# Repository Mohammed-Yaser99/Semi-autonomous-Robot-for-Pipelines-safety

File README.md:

This repository contains working files of a Semi-Autonomous Pipline Inspection robot "RC-XD" :
- Code files for : Arduino mega , Arduino Uno , Rasperry-pi , V-rep simulation
- PCBS design 
- Presenation and Report for detailed aspects and study cases of the project
- Video for the V-rep simulation

- Pipeline systems deteriorate progressively over time through various means.
- This product aims to create a pipeline inspection robot that has an adaptable structure to the pipe diameter, and cheap at the same time.
- Pipeline inspection robots are designed to act in inaccessible environment and also to remove the human factor from labour intensive or dangerous work environments. 
- Our challenge is to make this robot adaptable to pipe diameters varying from 450mm to 700mm with an adjustable probe mount.

- Adjustable diameter range (45-70 cm)
- Long travel ranges up to 30m
- Crack identification 
- Shape identification for cracks 
- Locating crack places
- Live video record 
- Electrically insulated 
- Scratch free wheels and safe to pipes insulation materials 
- Easy to transport 
- Easy interface

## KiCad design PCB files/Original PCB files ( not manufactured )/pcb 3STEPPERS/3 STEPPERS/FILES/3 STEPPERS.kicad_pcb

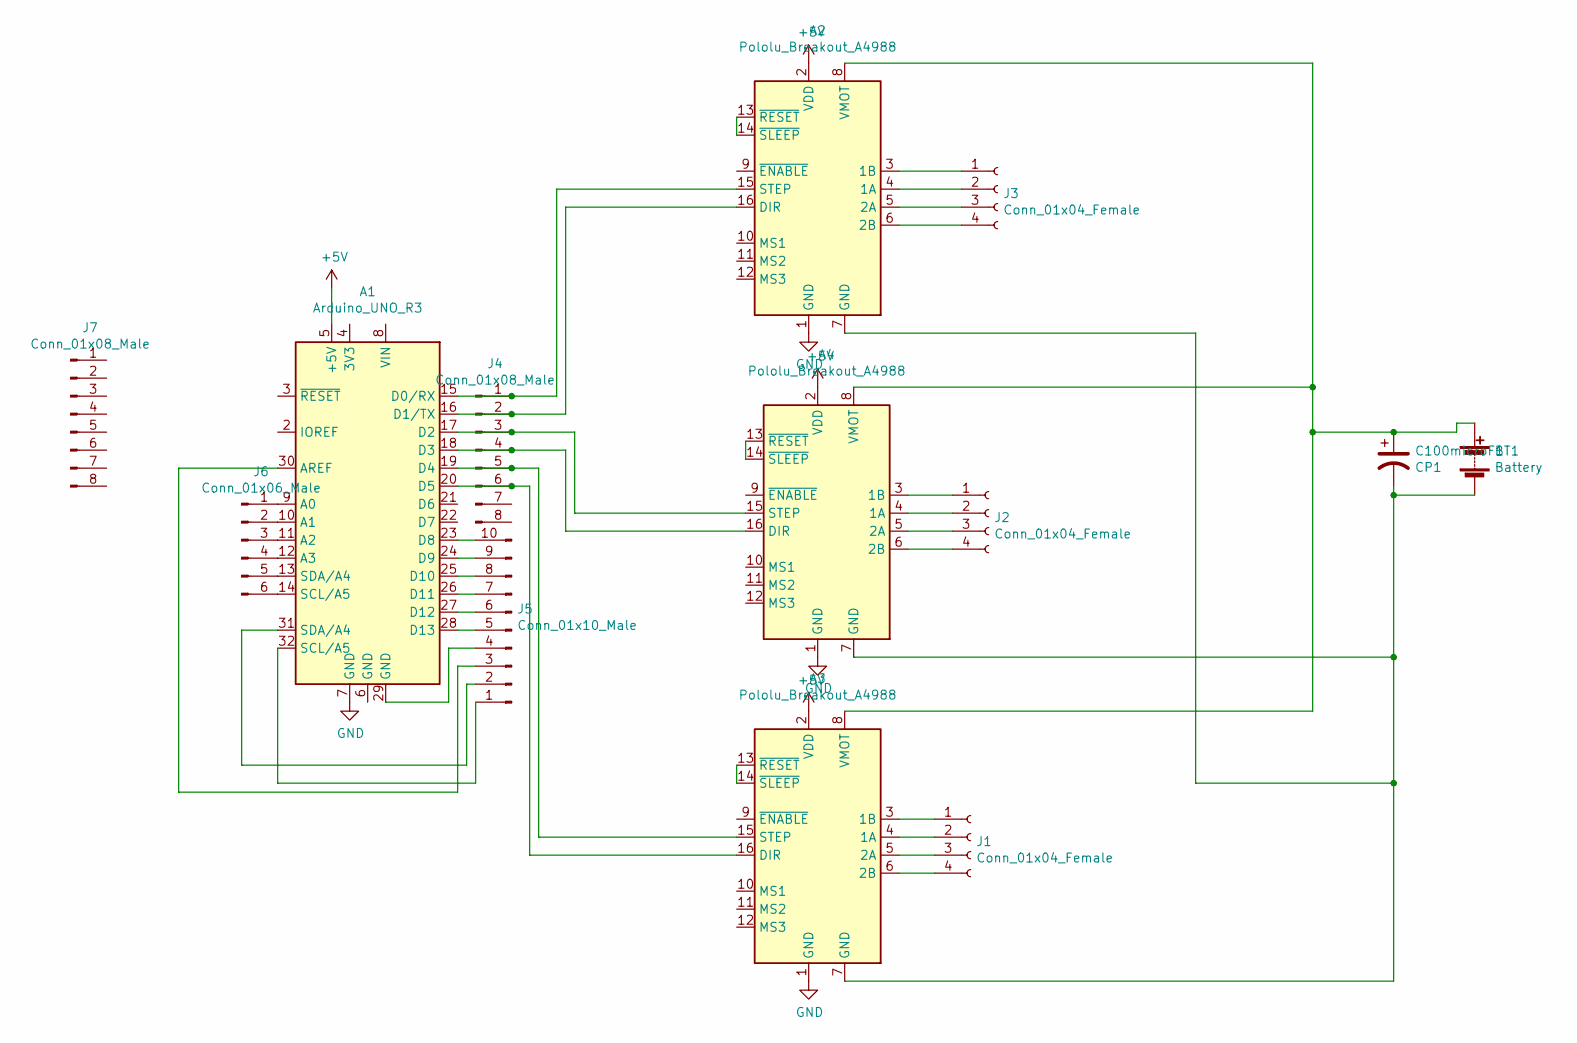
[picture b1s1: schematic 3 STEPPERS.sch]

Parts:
A1: Arduino_UNO_R3
A2, A3, A4: Pololu_Breakout_A4988; Pololu_Breakout-16_15.2x20.3mm
BT1: Battery; TerminalBlock_Phoenix_MKDS-1,5-2_1x02_P5.00mm_Horizontal
C100microF1: CP1; CP_Radial_D12.5mm_P7.50mm
J1, J2, J3: Conn_01x04_Female; PinSocket_1x04_P1.00mm_Vertical
J4, J7: Conn_01x08_Male; PinHeader_1x08_P2.54mm_Vertical
J5: Conn_01x10_Male; PinHeader_1x10_P2.54mm_Vertical
J6: Conn_01x06_Male; PinHeader_1x06_P2.54mm_Vertical

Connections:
+5V: A1.5 (+5V), A2.2 (VDD), A3.2 (VDD), A4.2 (VDD)
GND: A1.7 (GND), A2.1 (GND), A3.1 (GND), A4.1 (GND)
unnamed: A1.9 (A0), J6.1
unnamed: A1.10 (A1), J6.2
unnamed: A1.11 (A2), J6.3
unnamed: A1.12 (A3), J6.4
unnamed: A1.13 (SDA/A4), J6.5
unnamed: A1.14 (SCL/A5), J6.6
unnamed: A1.15 (D0/RX), A2.15 (STEP), J4.1
unnamed: A1.16 (D1/TX), A2.16 (DIR), J4.2
unnamed: A1.17 (D2), A4.15 (STEP), J4.3
unnamed: A1.18 (D3), A4.16 (DIR), J4.4
unnamed: A1.19 (D4), A3.15 (STEP), J4.5
unnamed: A1.20 (D5), A3.16 (DIR), J4.6
unnamed: A1.23 (D8), J5.10
unnamed: A1.24 (D9), J5.9
unnamed: A1.25 (D10), J5.8
unnamed: A1.26 (D11), J5.7
unnamed: A1.27 (D12), J5.6
unnamed: A1.28 (D13), J5.5
unnamed: A1.29 (GND), J5.4
unnamed: A1.30 (AREF), J5.3
unnamed: A1.31 (SDA/A4), J5.2
unnamed: A1.32 (SCL/A5), J5.1
unnamed: A2.3 (1B), J3.1
unnamed: A2.4 (1A), J3.2
unnamed: A2.5 (2A), J3.3
unnamed: A2.6 (2B), J3.4
unnamed: A2.7 (GND), A3.7 (GND), A4.7 (GND), BT1.2 (-), C100microF1.2
unnamed: A2.8 (VMOT), A3.8 (VMOT), A4.8 (VMOT), BT1.1 (+), C100microF1.1
unnamed: A2.13 (~RESET), A2.14 (~SLEEP)
unnamed: A3.3 (1B), J1.1
unnamed: A3.4 (1A), J1.2
unnamed: A3.5 (2A), J1.3
unnamed: A3.6 (2B), J1.4
unnamed: A3.13 (~RESET), A3.14 (~SLEEP)
unnamed: A4.3 (1B), J2.1
unnamed: A4.4 (1A), J2.2
unnamed: A4.5 (2A), J2.3
unnamed: A4.6 (2B), J2.4
unnamed: A4.13 (~RESET), A4.14 (~SLEEP)

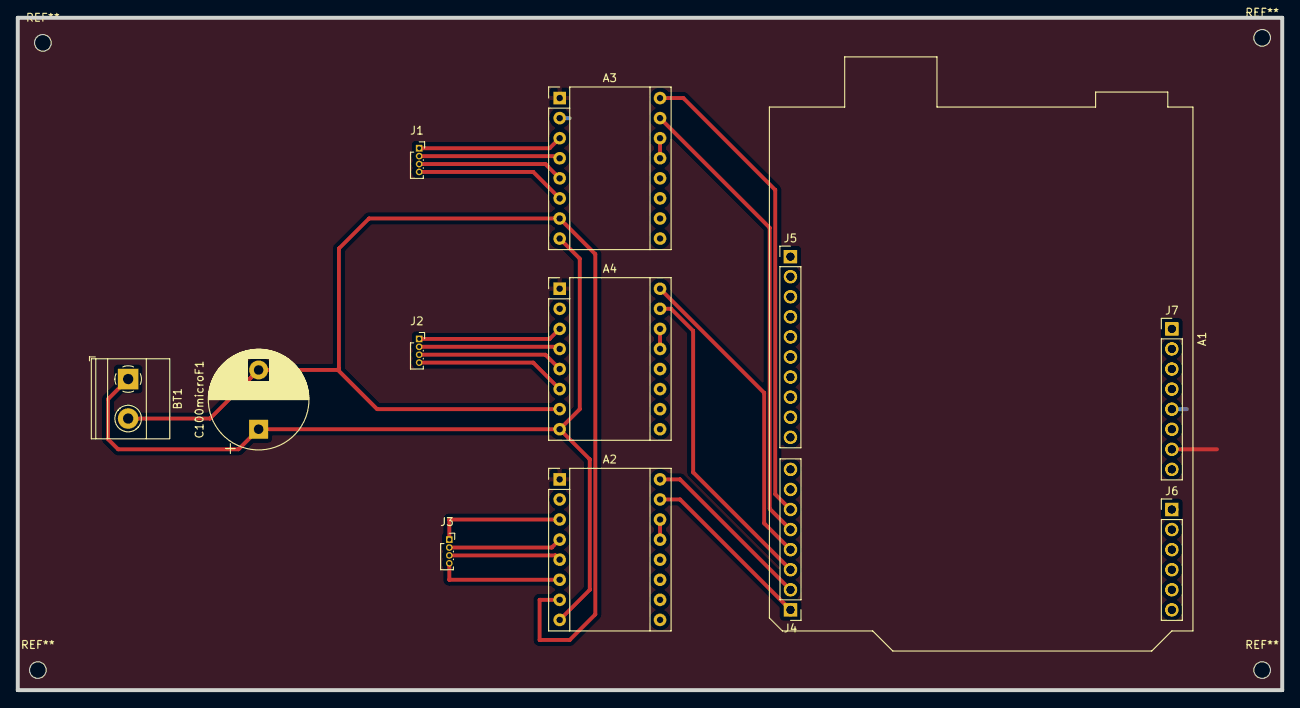
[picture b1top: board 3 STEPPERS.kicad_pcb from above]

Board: 2 copper layers, 160.0 x 85.1 mm, 13 parts (0 on the bottom side), 41 nets.

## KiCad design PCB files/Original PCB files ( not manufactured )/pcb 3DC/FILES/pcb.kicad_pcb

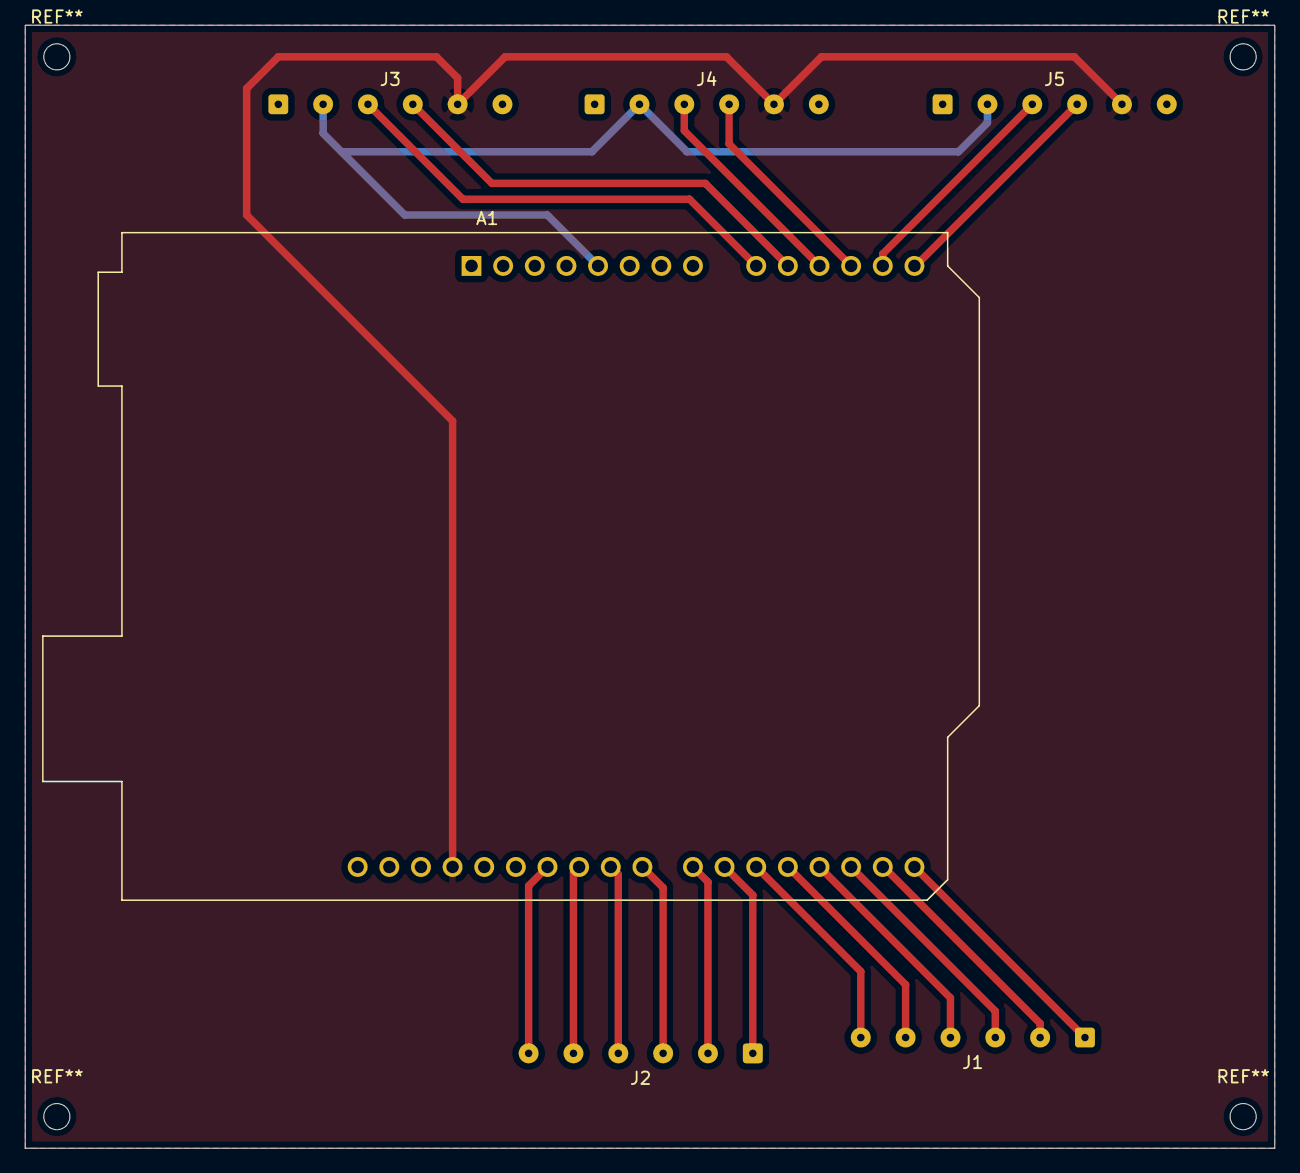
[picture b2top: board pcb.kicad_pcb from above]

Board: 2 copper layers, 100.3 x 90.2 mm, 6 parts (0 on the bottom side), 20 nets.

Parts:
A1: Arduino_UNO_R3
J1, J2, J3, J4, J5: Conn_01x06; SolderWire-0.1sqmm_1x06_P3.6mm_D0.4mm_OD1mm

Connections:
+5V: A1.5, J3.2, J4.2, J5.2
GND: A1.29, J3.5, J4.5, J5.5
unnamed: A1.9, J3.3
unnamed: A1.10, J3.4
unnamed: A1.11, J4.3
unnamed: A1.12, J4.4
unnamed: A1.13, J5.3
unnamed: A1.14, J5.4
unnamed: A1.15, J1.1
unnamed: A1.16, J1.2
unnamed: A1.17, J1.3
unnamed: A1.18, J1.4
unnamed: A1.19, J1.5
unnamed: A1.20, J1.6
unnamed: A1.21, J2.1
unnamed: A1.22, J2.2
unnamed: A1.23, J2.3
unnamed: A1.24, J2.4
unnamed: A1.25, J2.5
unnamed: A1.26, J2.6
